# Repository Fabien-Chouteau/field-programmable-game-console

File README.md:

# field-programmable-game-console
FPGC: A protable game console base on the TinyFPGA-BX

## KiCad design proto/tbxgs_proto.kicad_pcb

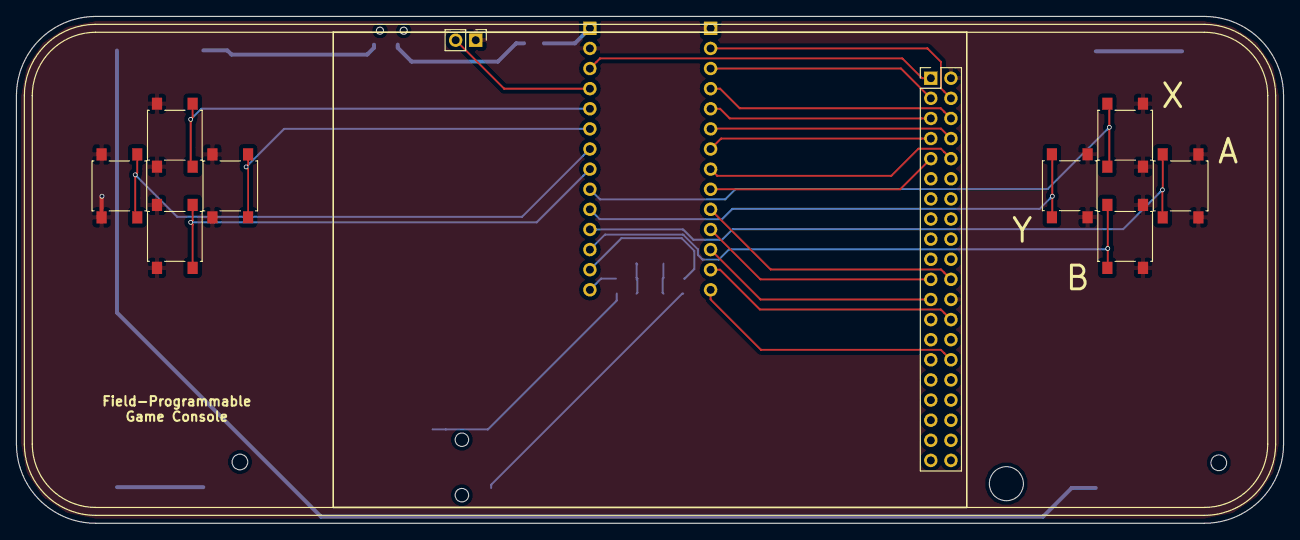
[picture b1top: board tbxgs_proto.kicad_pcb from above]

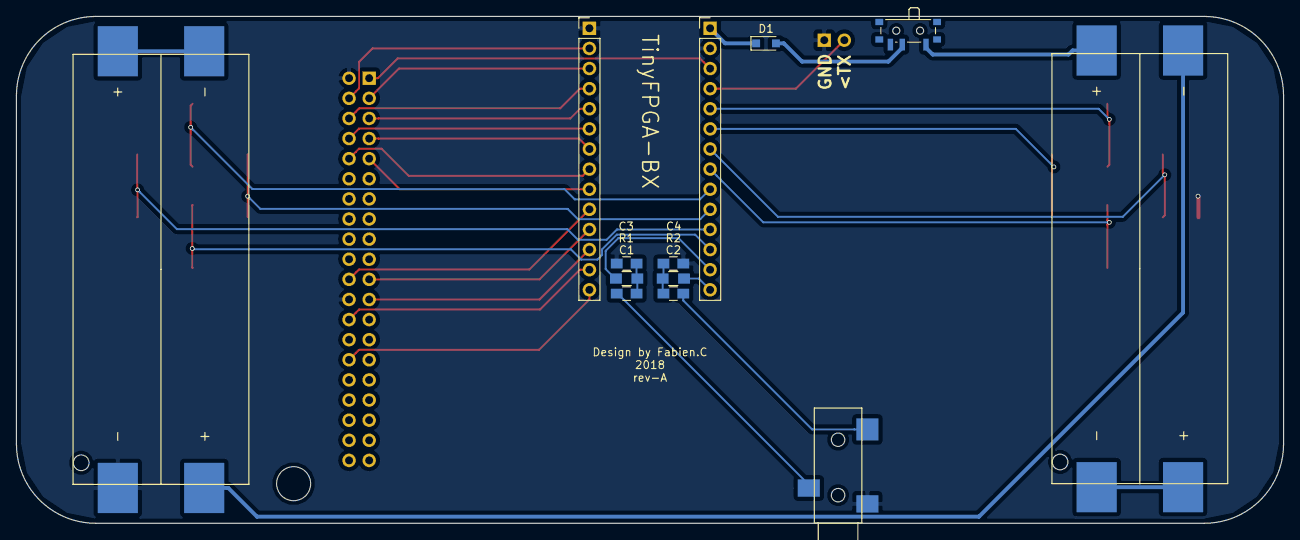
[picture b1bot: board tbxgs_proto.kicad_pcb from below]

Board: 2 copper layers, 160.0 x 64.0 mm, 23 parts (13 on the bottom side), 36 nets.

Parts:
BT1, BT2: Keystone 1022; DUAL_AAA_Battery_holder_1022
C1, C2: 10uF; C_0805_HandSoldering
C3, C4: 0.1uF; C_0805_HandSoldering
D1: DIODE; SOD-323_HandSoldering
J1: CONN_01X02; Pin_Header_Straight_1x02_Pitch2.54mm
J2: CONN_02X20; Pin_Header_Straight_2x20_Pitch2.54mm
J3, J5: CONN_01X14; Pin_Header_Straight_1x14_Pitch2.54mm
R1, R2: 330; R_0805_HandSoldering
SW1: SW_SPDT; SW_SPDT_PCM12
SWA1: B3FS-1010P; SW_SPST_B3S-1000
SWB1: B3FS-1010P; SW_SPST_B3S-1000
SWDOWN1: B3FS-1010P; SW_SPST_B3S-1000
SWLEFT1: B3FS-1010P; SW_SPST_B3S-1000
SWRIGHT1: B3FS-1010P; SW_SPST_B3S-1000
SWUP1: B3FS-1010P; SW_SPST_B3S-1000
SWX1: B3FS-1010P; SW_SPST_B3S-1000
SWY1: B3FS-1010P; SW_SPST_B3S-1000
U1: 3.5_audio_jack; SJ-3523-SMT

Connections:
/3V3: J2.1, J5.3
/A: J5.11, SWA1.2
/Audio_L: J5.14, R2.1
/Audio_R: J5.13, R1.1
/B: J5.12, SWB1.2
/DOWN: J5.8, SWDOWN1.2
/LCD_D0: J2.4, J3.2
/LCD_D1: J2.3, J3.3
/LCD_D2: J2.6, J3.4
/LCD_D3: J2.5, J3.5
/LCD_D4: J2.8, J3.6
/LCD_D5: J2.7, J3.7
/LCD_D6: J2.10, J3.8
/LCD_D7: J2.9, J3.9
/LCD_TE: J2.21, J3.11
/LCD_backlight: J2.30, J3.14
/LCD_datacmd: J2.23, J3.12
/LCD_nreset: J2.22, J3.10
/LCD_write_edge: J2.26, J3.13
/LEFT: J5.7, SWLEFT1.2
/RIGHT: J5.6, SWRIGHT1.2
/TX: J1.2, J5.4
/UP: J5.5, SWUP1.2
/VIN: D1.1, J5.1
/X: J5.9, SWX1.2
/Y: J5.10, SWY1.2
GND: BT1.1, C3.2, C4.2, J1.1, J2.2, J2.24, J3.1, J5.2, SWA1.1, SWB1.1, SWDOWN1.1, SWLEFT1.1, SWRIGHT1.1, SWUP1.1, SWX1.1, SWY1.1, U1.2
unnamed: BT1.2, BT1.4
unnamed: BT1.3, BT2.4
unnamed: BT2.1, BT2.3
unnamed: BT2.2, SW1.1
unnamed: C1.1, C3.1, R1.2
unnamed: C1.2, U1.3
unnamed: C2.1, C4.1, R2.2
unnamed: C2.2, U1.1
unnamed: D1.2, SW1.2

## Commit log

2018-10-20 Proto board rev-A
